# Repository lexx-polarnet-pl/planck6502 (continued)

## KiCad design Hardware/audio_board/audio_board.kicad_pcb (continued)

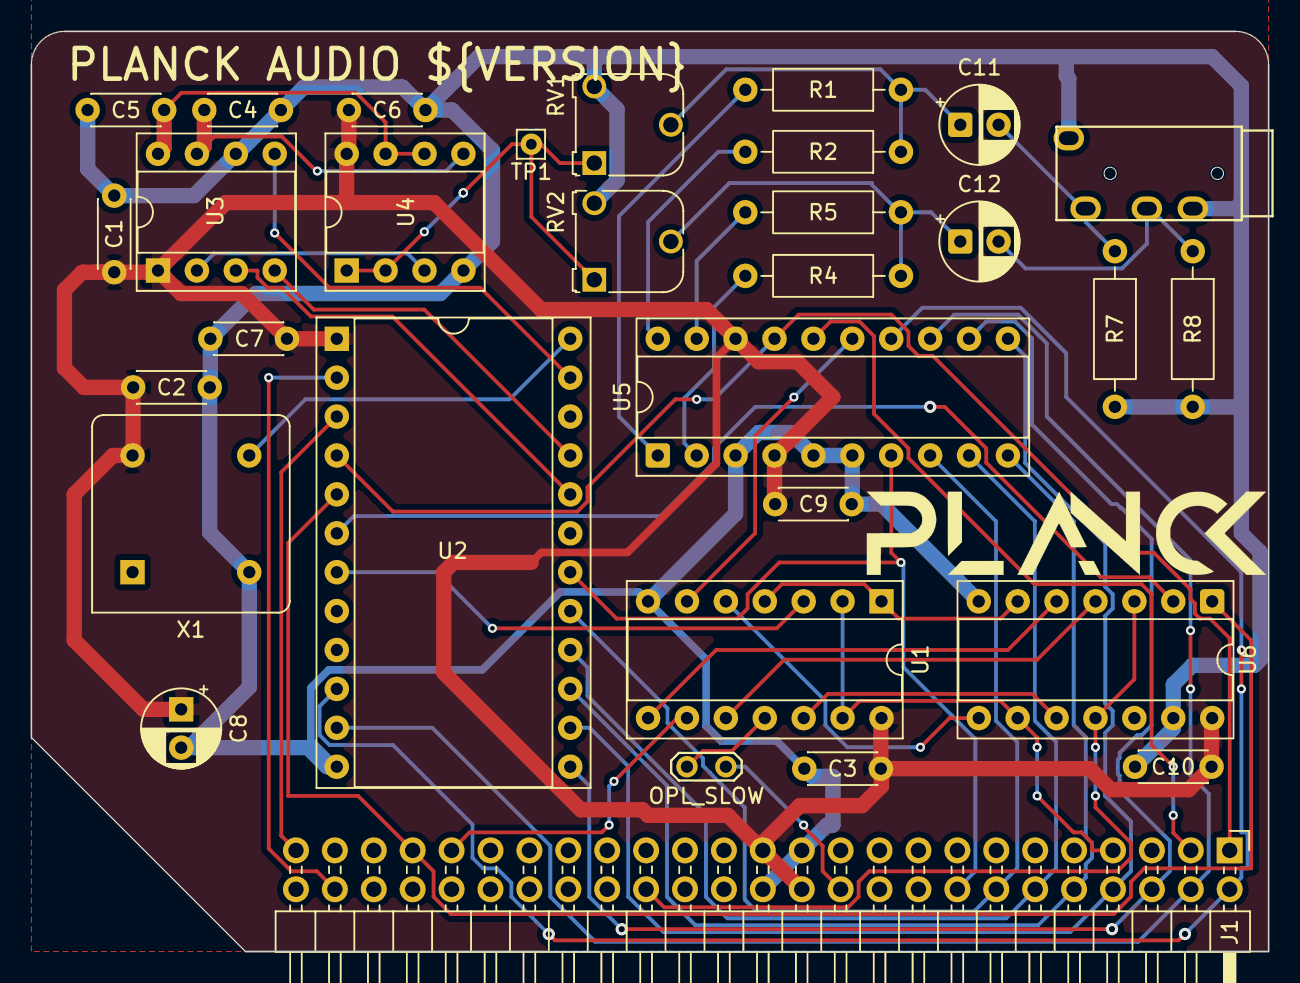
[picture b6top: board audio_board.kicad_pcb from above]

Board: 2 copper layers, 80.8 x 60.1 mm, 31 parts (0 on the bottom side), 44 nets.

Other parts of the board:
OPL_SLOW: OPL2 SLOW; TestPoint_2Pads_Pitch2.54mm_Drill0.8mm

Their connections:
unnamed 41: OPL_SLOW.1 (A); also elsewhere on the board
~SLOW: OPL_SLOW.2 (B); also elsewhere on the board

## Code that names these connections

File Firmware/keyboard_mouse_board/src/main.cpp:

#include <Arduino.h>

#include "keyboard.h"
#include "mouse.h"
#include "nvram.h"
#include "output.h"
#include "random.h"
#include "rtc.h"

static uint8_t nvram_address = 0;
static bool message_output_enabled = false;
static bool error_output_enabled = false;

constexpr uint8_t SYS_CTRL_IRQ_KBD_DATA = 1 << 0;
constexpr uint8_t SYS_CTRL_KEYBOARD_PRESENT = 1 << 5;
constexpr uint8_t SYS_CTRL_MOUSE_PRESENT = 1 << 6;
constexpr uint8_t SYS_CTRL_IRQ_ACTIVE = 1 << 7;
constexpr uint8_t SYS_CTRL_IRQ_GLOBAL_EN = 1 << 7;
constexpr uint8_t SYS_CTRL_IRQ_MASK = 0x87;
constexpr uint8_t SYS_CTRL_IRQ_SOURCE_MASK = 0x07;

static uint8_t irq_mask = 0;

uint8_t loopback = 0x55;

// Pinout ATmega328P
#define PIN_CS            PB0
#define PIN_RW            PB1
#define PIN_IRQ           PB2
#define PIN_RDY_STROBE    PB7

#define PIN_SDA           PC4
#define PIN_SCL           PC5

#define PIN_ADDR0         PC0
#define PIN_ADDR1         PC1
#define PIN_ADDR2         PC2
#define PIN_ADDR3         PC3

void show_message(const char* message)
{
    if (message_output_enabled)
    {
        kbd_push_string(message);
    }
}

void show_error(const char* message)
{
    if (error_output_enabled)
    {
        kbd_push_string(message);
    }
}

// ============================================================================
// OBSŁUGA MAGISTRALI DANYCH 6502
// ============================================================================
static inline void dataBusInput()
{
    DDRD = 0x00;
    PORTD = 0x00;
}

static inline void dataBusOutput(uint8_t value)
{
    PORTD = value;
    DDRD = 0xFF;
}

static inline bool csActive()
{
    return (PINB & _BV(PIN_CS)) == 0;
}

static inline bool isReadCycle()
{
    return (PINB & _BV(PIN_RW)) != 0;
}

static inline uint8_t getAddress()
{
    return PINC & 0x0F; // Odczyt A0-A3 z portu C (PC0-PC3)
}

static inline void rdyStrobe()
{
    PORTB &= ~_BV(PIN_RDY_STROBE);
    __asm__ __volatile__("nop\n\t");
    PORTB |= _BV(PIN_RDY_STROBE);
}

static uint8_t update_irq_state()
{
    uint8_t status = 0;
    if (keyboard_has_data())
    {
        status |= SYS_CTRL_IRQ_KBD_DATA;
    }

    uint8_t active_sources = status & irq_mask & SYS_CTRL_IRQ_SOURCE_MASK;
    if (active_sources != 0)
    {
        status |= SYS_CTRL_IRQ_ACTIVE;
    }

    if (active_sources != 0 && (irq_mask & SYS_CTRL_IRQ_GLOBAL_EN) != 0)
    {
        PORTB &= ~_BV(PIN_IRQ);
    }
    else
    {
        PORTB |= _BV(PIN_IRQ);
    }

    if (keyboard_is_present())
    {
        status |= SYS_CTRL_KEYBOARD_PRESENT;
    }
    if (mouse_is_present())
    {
        status |= SYS_CTRL_MOUSE_PRESENT;
    }

    return status;
}

// ============================================================================
// SETUP
// ============================================================================
void setup()
{
    dataBusInput();

    // Konfiguracja linii CS, RW, RDY
    DDRB &= ~(_BV(PIN_CS) | _BV(PIN_RW));
    DDRB |= _BV(PIN_IRQ) | _BV(PIN_RDY_STROBE);
    PORTB |= _BV(PIN_CS) | _BV(PIN_RW) | _BV(PIN_IRQ) | _BV(PIN_RDY_STROBE);

    // Konfiguracja adresów A0-A3 (PC0-PC3)
    DDRC &= ~(0x0F);

    rdyStrobe();

    show_message("\x1B[0m\x1B[2J\x1B[H"); // Clear screen

    nvram_init();
    rtc_init();
    random_init();
    keyboard_init();
    mouse_init();
    // TEMPORARY: remove this call after the first successful RTC test.
    // Otherwise every reboot resets the clock to this firmware's build time.
    //rtc_set_time_to_build_time();
}

// ============================================================================
// MAIN LOOP
// ============================================================================
void loop()
{
    // Release the shared data bus before the next 6502 cycle. A prior read
    // leaves DDRD configured as output until this point.
    dataBusInput();
    mouse_poll();

    if (!csActive())
    {
        keyboard_poll();
        mouse_poll();
        update_irq_state();
        return;
    }

    uint8_t addr = getAddress();

    if (isReadCycle())
    {
        switch (addr)
        {
            case 0x00: // KBD_DATA (BASE + $0)
                dataBusOutput(keyboard_read_data());
                break;

            case 0x01: // KBD_CTRL (BASE + $1)
                dataBusOutput(keyboard_read_control());
                break;

            case 0x02: // KBD_STAT (BASE + $2)
                dataBusOutput(keyboard_read_status());
                break;
            case 0x03: // loopback
                dataBusOutput(loopback);
                break;                

            case 0x06: // RTC_SEC (BASE + $6)
            case 0x07: // RTC_MIN (BASE + $7)
            case 0x08: // RTC_HOUR (BASE + $8)
            case 0x09: // RTC_DAY (BASE + $9)
            case 0x0A: // RTC_MONTH (BASE + $A)
            case 0x0B: // RTC_YEAR (BASE + $B)
            {
                uint8_t value = 0;
                if (rtc_read_register(addr - 0x06, value))
                {
                    dataBusOutput(value);
                }
                else
                {
                    dataBusOutput(0x00);
                }
                break;
            }

            case 0x0C: // NVRAM_ADDR (BASE + $C)
                dataBusOutput(nvram_address);
                break;

            case 0x0D: // NVRAM_DATA (BASE + $D)
                dataBusOutput(nvram_read(nvram_address));
                break;
            
            case 0x0E: // SYS_CTRL (BASE + $E)
                dataBusOutput(random_byte()); // RND generator
                break;

            case 0x0F: // SYS_CTRL_STAT (BASE + $F)
            {
                dataBusOutput(update_irq_state());
                break;
            }

            default:
                dataBusOutput(0x00);
                break;
        }
    }
    else // Cykl zapisu 6502 -> ATmega
    {
        uint8_t data_in = PIND; // Odczyt z magistrali
        switch (addr)
        {
            case 0x01: // KBD_CTRL (BASE + $1)
                keyboard_write_control(data_in);
                break;

            case 0x03: // loopback
                loopback = data_in;
                break;                

            case 0x06: // RTC_SEC (BASE + $6)
            case 0x07: // RTC_MIN (BASE + $7)
            case 0x08: // RTC_HOUR (BASE + $8)
            case 0x09: // RTC_DAY (BASE + $9)
            case 0x0A: // RTC_MONTH (BASE + $A)
            case 0x0B: // RTC_YEAR (BASE + $B)
                rtc_write_register(addr - 0x06, data_in);
                break;

            case 0x0C: // NVRAM_ADDR (BASE + $C)
                nvram_address = data_in;
                break;

            case 0x0D: // NVRAM_DATA (BASE + $D)
                nvram_write(nvram_address, data_in);
                break;

            case 0x0F: // SYS_CTRL_STAT (BASE + $F): IRQ_MASK
                irq_mask = data_in & SYS_CTRL_IRQ_MASK;
                break;
        }
    }

    update_irq_state();
    //delayMicroseconds(100);
    rdyStrobe();
}

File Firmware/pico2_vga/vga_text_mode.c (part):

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 * 
 *
 * HARDWARE CONNECTIONS
   - GPIO 16 ---> VGA Hsync 
   - GPIO 17 ---> VGA Vsync 
   - GPIO 18 ---> VGA Green lo-bit --> 470 ohm resistor --> VGA_Green
   - GPIO 19 ---> VGA Green hi_bit --> 330 ohm resistor --> VGA_Green
   - GPIO 20 ---> 330 ohm resistor ---> VGA-Blue 
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    // Read all GPIOs at once
    uint32_t gpio_state = sio_hw->gpio_in;    
    uint8_t data = 0;
    // GPIO4 -> bit7
    data |= ((gpio_state >> 4) & 1) << 7;
    // GPIO5 -> bit6
    data |= ((gpio_state >> 5) & 1) << 6;
    // GPIO6 -> bit5
    data |= ((gpio_state >> 6) & 1) << 5;
    // GPIO7 -> bit4
    data |= ((gpio_state >> 7) & 1) << 4;
    // GPIO8 -> bit3
    data |= ((gpio_state >> 8) & 1) << 3;
    // GPIO9 -> bit2
    data |= ((gpio_state >> 9) & 1) << 2;
    // GPIO10 -> bit1
    data |= ((gpio_state >> 10) & 1) << 1;
    // GPIO11 -> bit0
    data |= ((gpio_state >> 11) & 1);    
    buffer[head] = data;
    head = (head + 1) % BUFFER_SIZE;
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    // Store in circular buffer
    uint8_t data = 0;

    // GPIO4 -> bit7
    data |= ((gpio_state >> 4) & 1) << 7;

    // GPIO5 -> bit6
    data |= ((gpio_state >> 5) & 1) << 6;

    // GPIO6 -> bit5
    data |= ((gpio_state >> 6) & 1) << 5;

    // GPIO7 -> bit4
    data |= ((gpio_state >> 7) & 1) << 4;

    // GPIO8 -> bit3
    data |= ((gpio_state >> 8) & 1) << 3;

    // GPIO9 -> bit2
    data |= ((gpio_state >> 9) & 1) << 2;

    // GPIO10 -> bit1
    data |= ((gpio_state >> 10) & 1) << 1;

    // GPIO11 -> bit0
    data |= ((gpio_state >> 11) & 1);    
    buffer[head] = data;
    head = (head + 1) % BUFFER_SIZE;
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
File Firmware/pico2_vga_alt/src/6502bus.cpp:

#include "6502bus.h"
uint row = 10;

void irq_handler(uint gpio, uint32_t events) {
    (void)gpio;
    (void)events;

    // Read all GPIOs at once
    uint32_t gpio_state = sio_hw->gpio_in;

    // 1. Adres: GPIO0-GPIO3 (4 bity) - odwrócenie kolejności
    uint8_t address = 0;              
    // GPIO3 -> bit0
    address |= ((gpio_state >> 3) & 1);
    // GPIO2 -> bit1
    address |= ((gpio_state >> 2) & 1) << 1;
    // GPIO1 -> bit2
    //address |= ((gpio_state >> 1) & 1) << 2;
    // GPIO0 -> bit3
    //address |= ((gpio_state) & 1) << 3;


    bool is_read = (gpio_state & (1u << RW_PIN)) != 0;

    // 2. Dane: GPIO4-GPIO11 (8 bitów) - odwrócenie kolejności
    uint8_t d = (gpio_state >> 4) & 0xFF;
    d = ((d & 0x55) << 1) | ((d & 0xAA) >> 1);
    d = ((d & 0x33) << 2) | ((d & 0xCC) >> 2);
    d = ((d & 0x0F) << 4) | ((d & 0xF0) >> 4);
    uint8_t data = d;

    /*char buffer[32];
    int OldPrintX, OldPrintY;

    if (address != 0x0 && !is_read) {
        OldPrintX = PrintX;
        OldPrintY = PrintY;
        snprintf(buffer, sizeof(buffer), "Addr: %02X, Data: %02X", address, data);
        PrintSetPos(60,address);
        PrintText(buffer);
        PrintSetPos(60,row);
        PrintText(buffer);
        row++;
        PrintX = OldPrintX;
        PrintY = OldPrintY;
        if (row >= 30) {
            row = 10;
        }
    }*/

    switch (address) {

        case 0x0:
            if (!is_read) {
                terminal_push_to_buffer(data);
            }
            break;

        case 0x1:
            if (is_read) {
                // TODO: Handle reads from address $1.
            } else {
                MySprite.x = data;
                // TODO: Handle writes to address $1.
            }
            break;

        case 0x2:
            if (is_read) {
                // TODO: Handle reads from address $2.
            } else {
                MySprite.y = data;
                // TODO: Handle writes to address $2.
            }
            break;

        default:
            if (is_read) {
                // TODO: Handle reads from other addresses.
            } else {
                // TODO: Handle writes to other addresses.
            }
            break;
    }
}

void setup6502bus() {
    // Configure data pins
    for (int i = 0; i < 12; i++) {
        gpio_init(i);
        gpio_set_dir(i, false); // input
    }

    // Configure the read/write signal (6502: high = read, low = write).
    gpio_init(RW_PIN);
    gpio_set_dir(RW_PIN, false);

    // Configure interrupt pin
    gpio_init(CLK_PIN);
    gpio_set_dir(CLK_PIN, false);
    //gpio_set_irq_enabled_with_callback(CLK_PIN, GPIO_IRQ_EDGE_FALL, true, &irq_handler);    // jak na razie to działa najlepiej
    gpio_set_irq_enabled_with_callback(CLK_PIN, GPIO_IRQ_EDGE_RISE, true, &irq_handler);    
}

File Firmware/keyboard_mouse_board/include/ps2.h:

#ifndef PS2_H
#define PS2_H

#include <Arduino.h>

constexpr uint8_t PIN_PS2_KB_DATA = PB3;
constexpr uint8_t PIN_PS2_KB_CLK = PB4;
constexpr uint8_t PIN_PS2_MS_DATA = PB5;
constexpr uint8_t PIN_PS2_MS_CLK = PB6;

enum class Ps2TimeoutMode : uint8_t
{
    PollIterations,
    Milliseconds
};

enum class Ps2ReceiveError : uint8_t
{
    None,
    ClockTimeout,
    BadFrame,
    BadParity
};

struct Ps2ReceiveStatus
{
    Ps2ReceiveError error;
    uint8_t bit;
    uint16_t frame;
};

void ps2_release_line(uint8_t pin);
void ps2_pull_line_low(uint8_t pin);
bool ps2_wait_clock_level(uint8_t clock_pin,
                          bool high,
                          uint32_t timeout,
                          Ps2TimeoutMode timeout_mode);
bool ps2_receive_byte(uint8_t clock_pin,
                      uint8_t data_pin,
                      uint8_t& value,
                      uint32_t timeout,
                      Ps2TimeoutMode timeout_mode,
                      bool wait_for_idle_high,
                      Ps2ReceiveStatus& status);
bool ps2_send_byte(uint8_t clock_pin,
                   uint8_t data_pin,
                   uint8_t value,
                   uint8_t& response);
void keyboard_process_ps2_scancode(uint8_t code);

#endif

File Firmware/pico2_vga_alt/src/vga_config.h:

// ****************************************************************************
//                                 
//                            VGA configuration
//
// ****************************************************************************

// === Configuration
#define LAYERS		4	// total layers 1..4 (1 base layer + 3 overlapped layers)
#define SEGMAX		8	// max. number of video segment per video strip (size of 1 sSegm = 28 bytes)
#define STRIPMAX	8	// max. number of video strips (size of 1 sStrip = sSegm size*SEGMAX+4 = 228 bytes)
				// size of sScreen = sStrip size*STRIPMAX+4 = 1828 bytes

#define MAXX		640	// max. resolution in X direction (must be power of 4)
#define MAXY		480	// max. resolution in Y direction

#define MAXLINE		700	// max. number of scanlines (including sync and dark lines)

// === Scanline render buffers (800 pixels: default size of buffers = 2*4*(800+8+800+24)+800 = 13856 bytes
//    Requirements by format, base layer 0, 1 wrap X segment:
//	GF_GRAPH8 ... control buffer 16 bytes
//	GF_TILE8 ... control buffer "width"+8 bytes
//	GF_TILE16 ... control buffer "width/2"+8 bytes
//	GF_TILE32 ... control buffer "width/4"+8 bytes
//	GF_TILE64 ... control buffer "width/8"+8 bytes
//	GF_PROGRESS ... control buffer 24 bytes
//	other formats: data buffer "width" bytes, control buffer 16 bytes
#define DBUF0_MAX	(MAXX+8)	// max. size of data buffer of layer 0
#define CBUF0_MAX	((MAXX+24)/4)	// max. size of control buffer of layer 0

//    Requirements by format, overlapped layer 1..3:
//	LAYERMODE_SPRITE* ... data buffer "width"+4 bytes, control buffer 24 bytes
//	LAYERMODE_FASTSPRITE* ... data buffer "width"+4 bytes, control buffer up to "width*2"+16 bytes
//	other formats ... data buffer 4 bytes, control buffer 24 bytes
#define DBUF1_MAX	(MAXX+8)	// max. size of data buffer of layer 1
#define CBUF1_MAX	((MAXX+24)/4)	// max. size of control buffer of layer 1

#define DBUF2_MAX	(MAXX+8)	// max. size of data buffer of layer 2
#define CBUF2_MAX	((MAXX+24)/4)	// max. size of control buffer of layer 2

#define DBUF3_MAX	(MAXX+8)	// max. size of data buffer of layer 3
#define CBUF3_MAX	((MAXX+24)/4)	// max. size of control buffer of layer 3

#if LAYERS==1
#define	DBUF_MAX	DBUF0_MAX	// max. size of data buffer
#define	CBUF_MAX	CBUF0_MAX	// max. size of control buffer
#elif LAYERS==2
#define	DBUF_MAX	(DBUF0_MAX+DBUF1_MAX)	// max. size of data buffer
#define	CBUF_MAX	(CBUF0_MAX+CBUF1_MAX)	// max. size of control buffer
#elif LAYERS==3
#define	DBUF_MAX	(DBUF0_MAX+DBUF1_MAX+DBUF2_MAX)	// max. size of data buffer
#define	CBUF_MAX	(CBUF0_MAX+CBUF1_MAX+CBUF2_MAX)	// max. size of control buffer
#elif LAYERS==4
#define	DBUF_MAX	(DBUF0_MAX+DBUF1_MAX+DBUF2_MAX+DBUF3_MAX) // max. size of data buffer
#define	CBUF_MAX	(CBUF0_MAX+CBUF1_MAX+CBUF2_MAX+CBUF3_MAX) // max. size of control buffer
#else
#error Unsupported number of layers!
#endif

// === VGA port pins
//	GP0 ... VGA B0 blue
//	GP1 ... VGA B1
//	GP2 ... VGA G0 green
//	GP3 ... VGA G1
//	GP4 ... VGA G2
//	GP5 ... VGA R0 red
//	GP6 ... VGA R1
//	GP7 ... VGA R2
//	GP8 ... VGA SYNC synchronization (inverted: negative SYNC=LOW=0x80, BLACK=HIGH=0x00)
#define VGA_GPIO_FIRST	14	// first VGA GPIO
#define VGA_GPIO_NUM	9	// number of VGA GPIOs, including HSYNC and VSYNC
#define VGA_GPIO_OUTNUM	8	// number of VGA color GPIOs, without HSYNC and VSYNC
#define VGA_GPIO_LAST	(VGA_GPIO_FIRST+VGA_GPIO_NUM-1)	// last VGA GPIO
#define VGA_GPIO_SYNC	22	// VGA SYNC GPIO

// VGA PIO and state machines
#define VGA_PIO		pio0	// VGA PIO
#define VGA_SM0		0	// VGA state machine of base layer 0
#define VGA_SM1		1	// VGA state machine of overlapped layer 1
#define VGA_SM2		2	// VGA state machine of overlapped layer 2
#define VGA_SM3		3	// VGA state machine of overlapped layer 3
#define VGA_SM(layer)	(VGA_SM0+(layer)) // VGA state machine of the layer

#if LAYERS==1
#define VGA_SMALL	B0	// mask of all state machines
#elif LAYERS==2
#define VGA_SMALL	(B0+B1) // mask of all state machines
#elif LAYERS==3
#define VGA_SMALL	(B0+B1+B2) // mask of all state machines
#elif LAYERS==4
#define VGA_SMALL	(B0+B1+B2+B3) // mask of all state machines
#else
#error Unsupported number of layers!
#endif

// VGA DMA
#define VGA_DMA		0		// VGA DMA base channel
#define VGA_DMA_CB0	(VGA_DMA+0)	// VGA DMA channel - control block of base layer
#define VGA_DMA_PIO0	(VGA_DMA+1)	// VGA DMA channel - copy data of base layer to PIO (raises IRQ0 on quiet)
#define VGA_DMA_CB1	(VGA_DMA+2)	// VGA DMA channel - control block of overlapped layer 1
#define VGA_DMA_PIO1	(VGA_DMA+3)	// VGA DMA channel - copy data of overlapped layer 1 to PIO
#define VGA_DMA_CB2	(VGA_DMA+4)	// VGA DMA channel - control block of overlapped layer 1
#define VGA_DMA_PIO2	(VGA_DMA+5)	// VGA DMA channel - copy data of overlapped layer 2 to PIO
#define VGA_DMA_CB3	(VGA_DMA+6)	// VGA DMA channel - control block of overlapped layer 1
#define VGA_DMA_PIO3	(VGA_DMA+7)	// VGA DMA channel - copy data of overlapped layer 3 to PIO

#define VGA_DMA_CB(layer) (VGA_DMA_CB0+(layer)*2) // VGA DMA control channel of the layer
#define VGA_DMA_PIO(layer) (VGA_DMA_PIO0+(layer)*2) // VGA DMA data channel of the layer

#define VGA_DMA_NUM	(LAYERS*2)	// number of used DMA channels
#define VGA_DMA_FIRST	VGA_DMA		// first used DMA
#define VGA_DMA_LAST	(VGA_DMA_FIRST+VGA_DMA_NUM-1) // last used DMA

#define USE_SPRITES 1  // 1 = włącz duszki, 0 = wyłącz
